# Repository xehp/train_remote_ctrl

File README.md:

# Train remote ctrl

In this project the aim is to make a model railway engine with a builtin web camera.

Hopefully the train can also be controled via the web page.

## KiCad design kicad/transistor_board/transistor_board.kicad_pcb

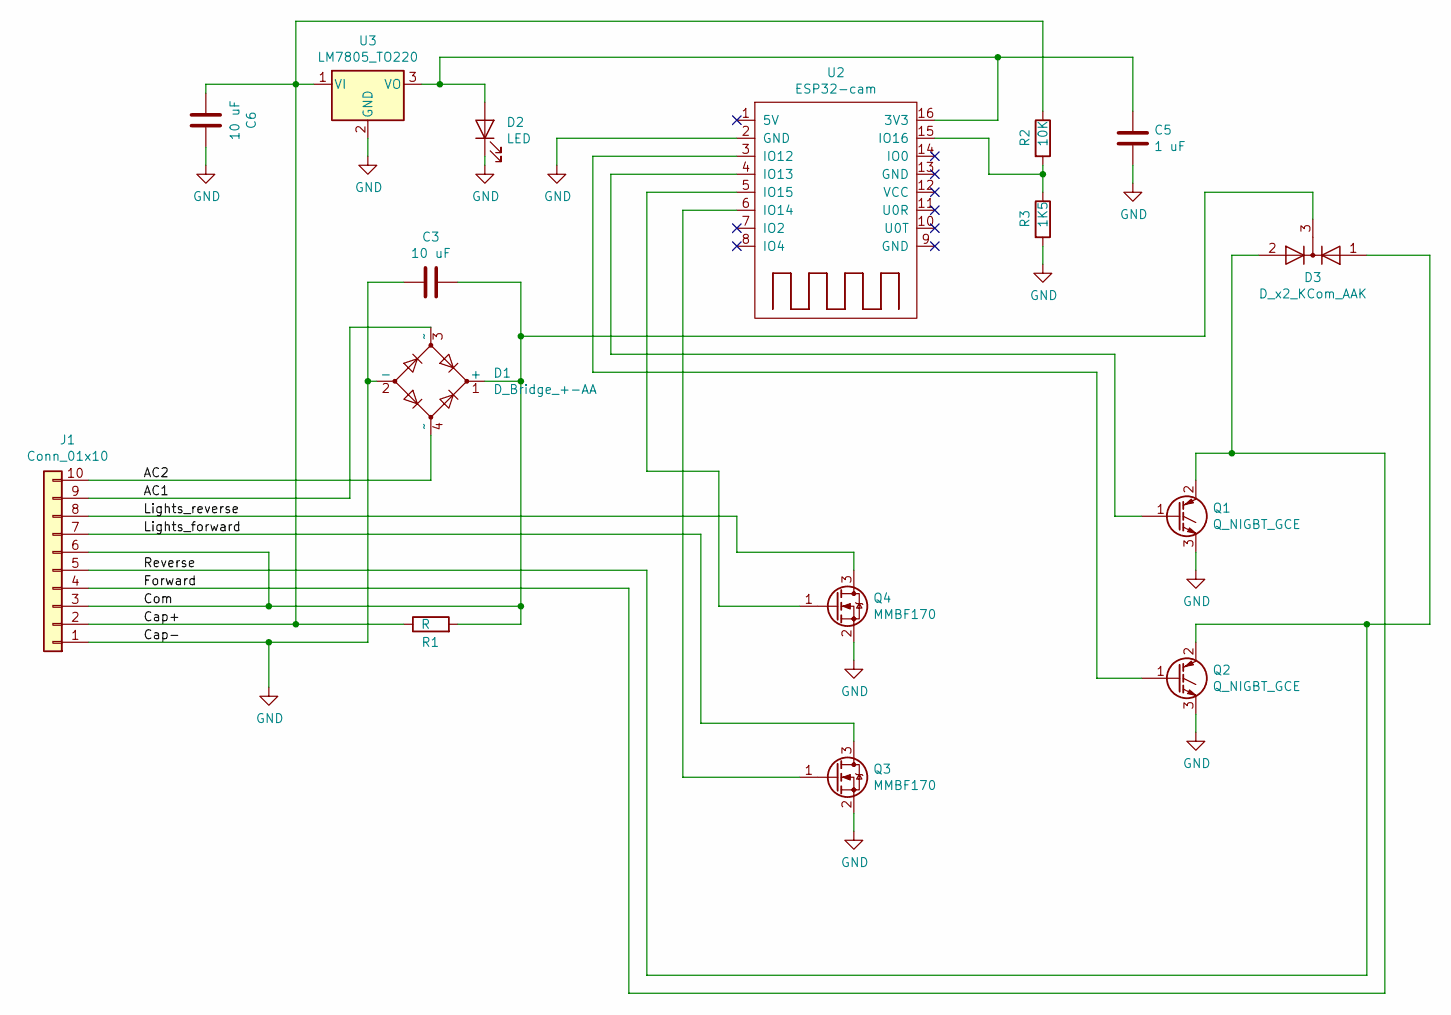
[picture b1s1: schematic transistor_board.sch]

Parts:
C3, C6: 10 uF; C_1206_3216Metric
C5: 1 uF; C_0805_2012Metric
D1: D_Bridge_+-AA; Diode_Bridge_Vishay_DFS
D2: LED; LED_D3.0mm
D3: D_x2_KCom_AAK; SOT-23-3
J1: Conn_01x10; PinHeader_1x10_P2.54mm_Vertical
Q1, Q2: Q_NIGBT_GCE; TO-252-3_TabPin2
Q3, Q4: MMBF170; SOT-23
R1: R; R_2512_6332Metric
R2: 10K; R_0805_2012Metric_Pad1.15x1.40mm_HandSolder
R3: 1K5; R_0805_2012Metric_Pad1.15x1.40mm_HandSolder
U2: ESP32-cam; ESP32-CAM-10pin
U3: LM7805_TO220; TO-220-3_Vertical

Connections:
/AC1: D1.3 (~~), J1.9
/AC2: D1.4 (~~), J1.10
/Cap+: C6.2, J1.2, R1.1, R2.1, U3.1 (VI)
/Com: C3.1, D1.1 (+), D3.3 (K), J1.3, J1.6, R1.2
/Forward: D3.2 (A), J1.4, Q1.2 (C)
/Lights_forward: J1.7, Q3.3 (D)
/Lights_reverse: J1.8, Q4.3 (D)
/Reverse: D3.1 (A), J1.5, Q2.2 (C)
GND: C3.2, C5.2, C6.1, D1.2 (-), D2.1 (K), J1.1, Q1.3 (E), Q2.3 (E), Q3.2 (S), Q4.2 (S), R3.2, U2.2 (GND), U3.2 (GND)
unnamed: C5.1, D2.2 (A), U2.16 (3V3), U3.3 (VO)
unnamed: Q1.1 (G), U2.4 (IO13)
unnamed: Q2.1 (G), U2.3 (IO12)
unnamed: Q3.1 (G), U2.6 (IO14)
unnamed: Q4.1 (G), U2.5 (IO15)
unnamed: R2.2, R3.1, U2.15 (IO16)

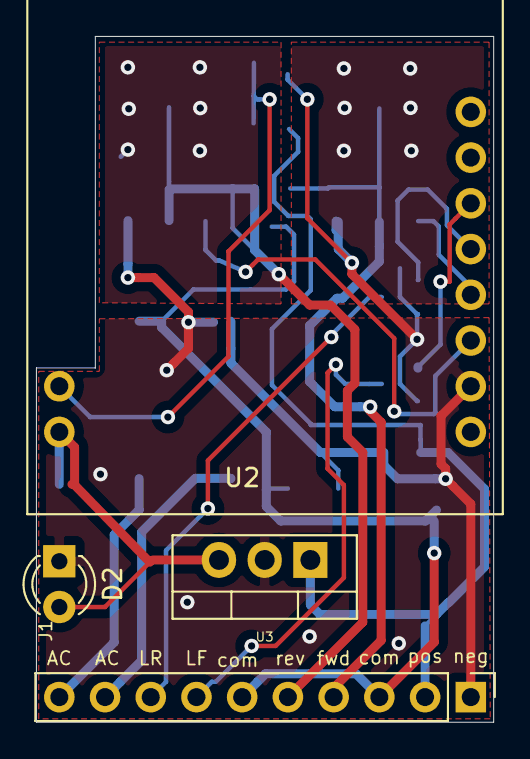
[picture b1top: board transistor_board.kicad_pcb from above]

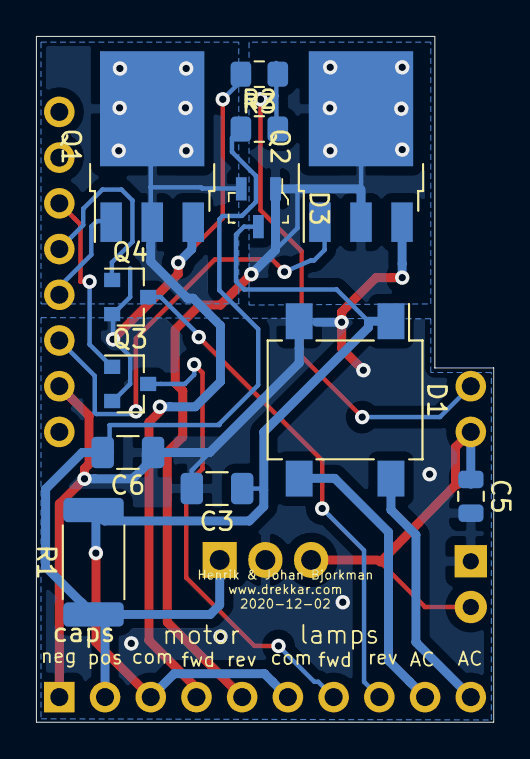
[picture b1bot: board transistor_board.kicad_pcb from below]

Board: 2 copper layers, 25.4 x 38.1 mm, 16 parts (12 on the bottom side), 15 nets.

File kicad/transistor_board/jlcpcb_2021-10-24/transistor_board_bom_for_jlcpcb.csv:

Comment,Designator,Footprint,LCSC
"1 uF","C5","Capacitor_SMD:C_0805_2012Metric",""
"10 uF","C3,C6","Capacitor_SMD:C_1206_3216Metric",""
"D_Bridge_+-AA","D1","Diode_SMD:Diode_Bridge_Vishay_DFS",""
"LED","D2","LED_THT:LED_D3.0mm",""
"D_x2_KCom_AAK","D3","digikey-footprints:SOT-23-3",""
"Conn_01x10","J1","Connector_PinHeader_2.54mm:PinHeader_1x10_P2.54mm_Vertical",""
"Q_NIGBT_GCE","Q1,Q2","Package_TO_SOT_SMD:TO-252-3_TabPin2",""
"MMBF170","Q3,Q4","Package_TO_SOT_SMD:SOT-23",""
"R","R1","Resistor_SMD:R_2512_6332Metric",""
"10K","R2","Resistor_SMD:R_0805_2012Metric_Pad1.15x1.40mm_HandSolder",""
"1K5","R3","Resistor_SMD:R_0805_2012Metric_Pad1.15x1.40mm_HandSolder",""
"ESP32-cam","U2","eit_footprints:ESP32-CAM",""
"LM7805_TO220","U3","Package_TO_SOT_THT:TO-220-3_Vertical",""

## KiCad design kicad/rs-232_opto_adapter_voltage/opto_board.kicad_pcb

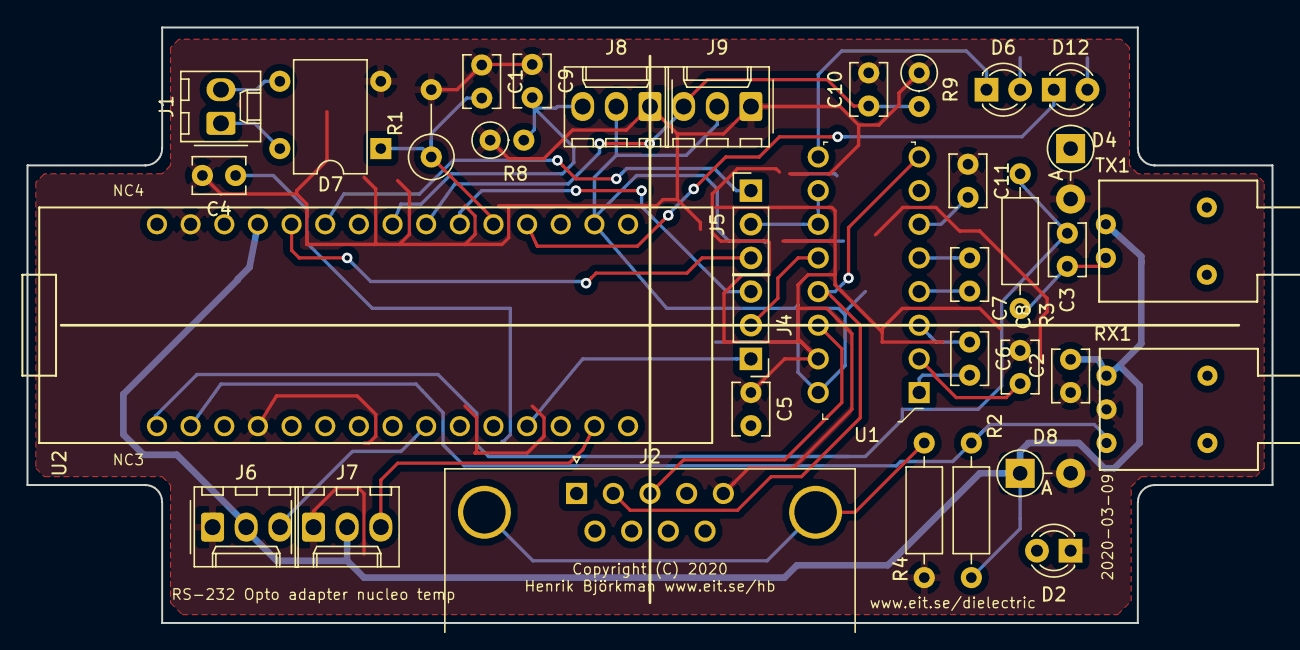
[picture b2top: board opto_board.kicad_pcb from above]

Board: 2 copper layers, 94.0 x 45.0 mm, 35 parts (0 on the bottom side), 30 nets.

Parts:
C1, C2, C3, C4, C5, C6, C7, C8, C9, C10, C11: C; C_Disc_D3.8mm_W2.6mm_P2.50mm
D2, D6, D12: LED; LED_D3.0mm
D4, D8: D_Zener; D_DO-41_SOD81_P3.81mm_Vertical_AnodeUp
D7: D_Bridge_+-AA; Diode_Bridge_DIP-4_W7.62mm_P5.08mm
J1: Conn_01x02; Molex_KK-254_AE-6410-02A_1x02_P2.54mm_Vertical
J2: DB9_Male_MountingHoles-Connector; DSUB-9_Male_Horizontal_P2.77x2.84mm_EdgePinOffset7.70mm_Hou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
J4, J5: Conn_01x03; PinHeader_1x03_P2.54mm_Vertical
J6, J7, J8, J9: Conn_01x03; Molex_KK-254_AE-6410-03A_1x03_P2.54mm_Vertical
R1: R; R_Axial_DIN0309_L9.0mm_D3.2mm_P5.08mm_Vertical
R2, R3, R4: R; R_Axial_DIN0207_L6.3mm_D2.5mm_P10.16mm_Horizontal
R8, R9: R; R_Axial_DIN0207_L6.3mm_D2.5mm_P2.54mm_Vertical
RX1: opto_receiver_broadcom; opto_receiver_broadwell
TX1: opto_transmitter_broadcom; opto_transmitter_broadwell
U1: MAX232N-dk_Interface-Drivers-Receivers-Transceive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; DIP-16_W7.62mm
U2: nucleo_nano

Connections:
+3V3: C4.2, C5.2, D2.2, D4.1, D6.2, D12.2, J8.2, J9.2, U1.16, U2.17
+5V: C2.2, D8.1, J6.2, J7.2, R2.2, RX1.1, TX1.1, U2.27
GND: C1.1, C2.1, C4.1, C5.1, C8.1, C9.1, C10.1, C11.1, D2.1, D4.2, D7.2, D8.2, J2.5, J6.1, J7.1, J8.1, J9.1, R1.2, R4.2, R8.1, R9.1, RX1.2, U1.15, U2.4, U2.29
unnamed: C1.2, D7.1, R1.1, U2.20
unnamed: C3.1, R3.1, TX1.2
unnamed: C3.2, R3.2, U2.1
unnamed: C6.1, U1.3
unnamed: C6.2, U1.1
unnamed: C7.1, U1.5
unnamed: C7.2, U1.4
unnamed: C8.2, U1.2
unnamed: C9.2, J8.3, R8.2, U2.23
unnamed: C10.2, J9.3, R9.2, U2.22
unnamed: C11.2, U1.6
unnamed: D6.1, U1.9
unnamed: D7.3, J1.2
unnamed: D7.4, J1.1
unnamed: D12.1, U2.19
unnamed: J2.0, R4.1
unnamed: J2.2, U1.8, U1.13
unnamed: J2.3, U1.14
unnamed: J4.1, U2.12
unnamed: J4.2, U1.12
unnamed: J4.3, U2.21
unnamed: J5.1, U2.25
unnamed: J5.2, U1.10, U1.11
unnamed: J5.3, U2.26
unnamed: J6.3, U2.9
unnamed: J7.3, U2.14
unnamed: R2.1, RX1.3, U2.2

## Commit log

2020-07-21 first version
2020-07-29 transistor_board
2020-08-01 motor not powered via resistor
2020-08-02 working on footprints for transistor_board
2020-08-02 added footprints
2020-08-02 updated for newer libraries
2020-08-02 working on PCB layout
2020-08-02 changed some footprints
2020-08-02 routed all
2020-08-02 some text on PCB
2020-08-03 adjusting the PCB
2020-08-03 gerber files
2020-08-16 made cut out for connecting serial port
2020-09-12 remember: To enable download connect GPIO0/IO0 to GND.
2020-09-12 updated doc/esp32-cam.txt
2020-09-20 Camera Web Server —> LED Illuminator -> enable
2020-09-27 Transistors failed, need to use bigger, such as D-Pak (TO252AA)
2020-09-29 Working on bigger transistors
2020-09-30 IRLR120NPBFTR
2020-10-01 routing on transistor board
2020-10-04 Using ESP32-Cam with 10 pin footprint
2020-10-05 updated gerber files, sent to jlcpcb
2020-10-09 kicad/transistor_board/bom.txt
2020-10-20 updated bom
2020-10-24 TODO add an LED
2021-04-05 corrected the transistors
2021-04-05 prepared ordering more PCBs from JLCPCB
2021-10-25 prepared files to send to JLCPCB for assembly
2021-11-04 first version for github
2021-11-04 added LICENSE & README.md

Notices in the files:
kicad/rs-232_opto_adapter_voltage/opto_board.kicad_pcb:
Copyright (C) 2020
